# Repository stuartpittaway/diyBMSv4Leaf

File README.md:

# diyBMS v4

Version 4 of the diyBMS for Nissan Leaf Cells

Do it yourself battery management system for Lithium ion battery packs/cells

This circuit revision has been made by George Boudreau - using the original v4 BMS design by Stuart Pittaway.

To contact George, please message on https://community.openenergymonitor.org/

# Videos on how to use and build

https://www.youtube.com/stuartpittaway

# CODE/SOFTWARE

Software and code for the modules and controller can now be found in a seperate repo

https://github.com/stuartpittaway/diyBMSv4Code

# WARNING

This is a DIY product/solution so don’t use this for safety critical systems or in any situation where there could be a risk to life.  

There is no warranty, it may not work as expected or at all.

The use of this project is done so entirely at your own risk.  It may involve electrical voltages which could kill - if in doubt, seek help.

The use of this project may not be compliant with local laws or regulations - if in doubt, seek help.

# License

This work is licensed under a Creative Commons Attribution-NonCommercial-ShareAlike 2.0 UK: England & Wales License.

https://creativecommons.org/licenses/by-nc-sa/2.0/uk/

You are free to:
* Share — copy and redistribute the material in any medium or format
* Adapt — remix, transform, and build upon the material
The licensor cannot revoke these freedoms as long as you follow the license terms.

Under the following terms:
* Attribution — You must give appropriate credit, provide a link to the license, and indicate if changes were made. You may do so in any reasonable manner, but not in any way that suggests the licensor endorses you or your use.
* Non-Commercial — You may not use the material for commercial purposes.
* ShareAlike — If you remix, transform, or build upon the material, you must distribute your contributions under the same license as the original.
* No additional restrictions — You may not apply legal terms or technological measures that legally restrict others from doing anything the license permits.

Notices:
You do not have to comply with the license for elements of the material in the public domain or where your use is permitted by an applicable exception or limitation.

No warranties are given. The license may not give you all of the permissions necessary for your intended use. For example, other rights such as publicity, privacy, or moral rights may limit how you use the material.

# Problem

A DIY Powerwall is the DIY construction of a pack of battery cells to create an energy store which can be used via inverters to power electrical items in the home. Generally cells are salvaged/second hand, and typically use Lithium 18650 cells.

Lithium batteries need to be kept at the same voltage level across a parallel pack. This is done by balancing each cell in the pack to raise or lower its voltage to match the others.

Existing balancing solutions are available in the market place, but at a relatively high cost compared to the cost of the battery bank, so this project is to design a low-cost, simple featured BMS/balancer.

# BMS Design

Design Goals: 
* Build upon my existing skill set and knowledge. 
* Building something that others can contribute to using regular standard libraries and off the shelf components.
* Build something that is inheriently safe
* Use platform.io to manage code and libraries
* Use Arduino based libraries and tools 
* Put everything on GITHUB
* Document it (always gets left to the end!)

# How it works

Controller provides human interface over Wifi/Web and also integrates with other systems like MQTT, emonCMS and Grafana.

Controller is esp8266-12e (NodeMCU v1) - although could be upgraded to ESP32 if really needed.

Controller should be able to take action on alerts/events to shut down inverters/chargers/fuses.

Each cell in a battery pack has a monitoring module.  This uses AVR ATTINY841 linked together by optoisolated serial ports for communication.

ATTINY841 provides:
* internal temperature monitoring
* external temperature monitoring
* Spare input/output for 3rd party use
* autonomous cell voltage balancing - it should still work even if controller is down

# How as v4 improved over v3?

* Code is better!
* Web interface no longer requires access to internet to download javascript libraries
* Controller provides outputs for integration with relay boards and switch gear
* Rules to control relay outputs
* Cell modules use ATTINY841 chip which provides more pins and lower power usage
* Removal of 3.3v regulator and ADUM chips lowers current usage significantly
* v3 module uses 10-12mA current constantly and v4 uses <1mA
* Dual temperature monitoring board + cells

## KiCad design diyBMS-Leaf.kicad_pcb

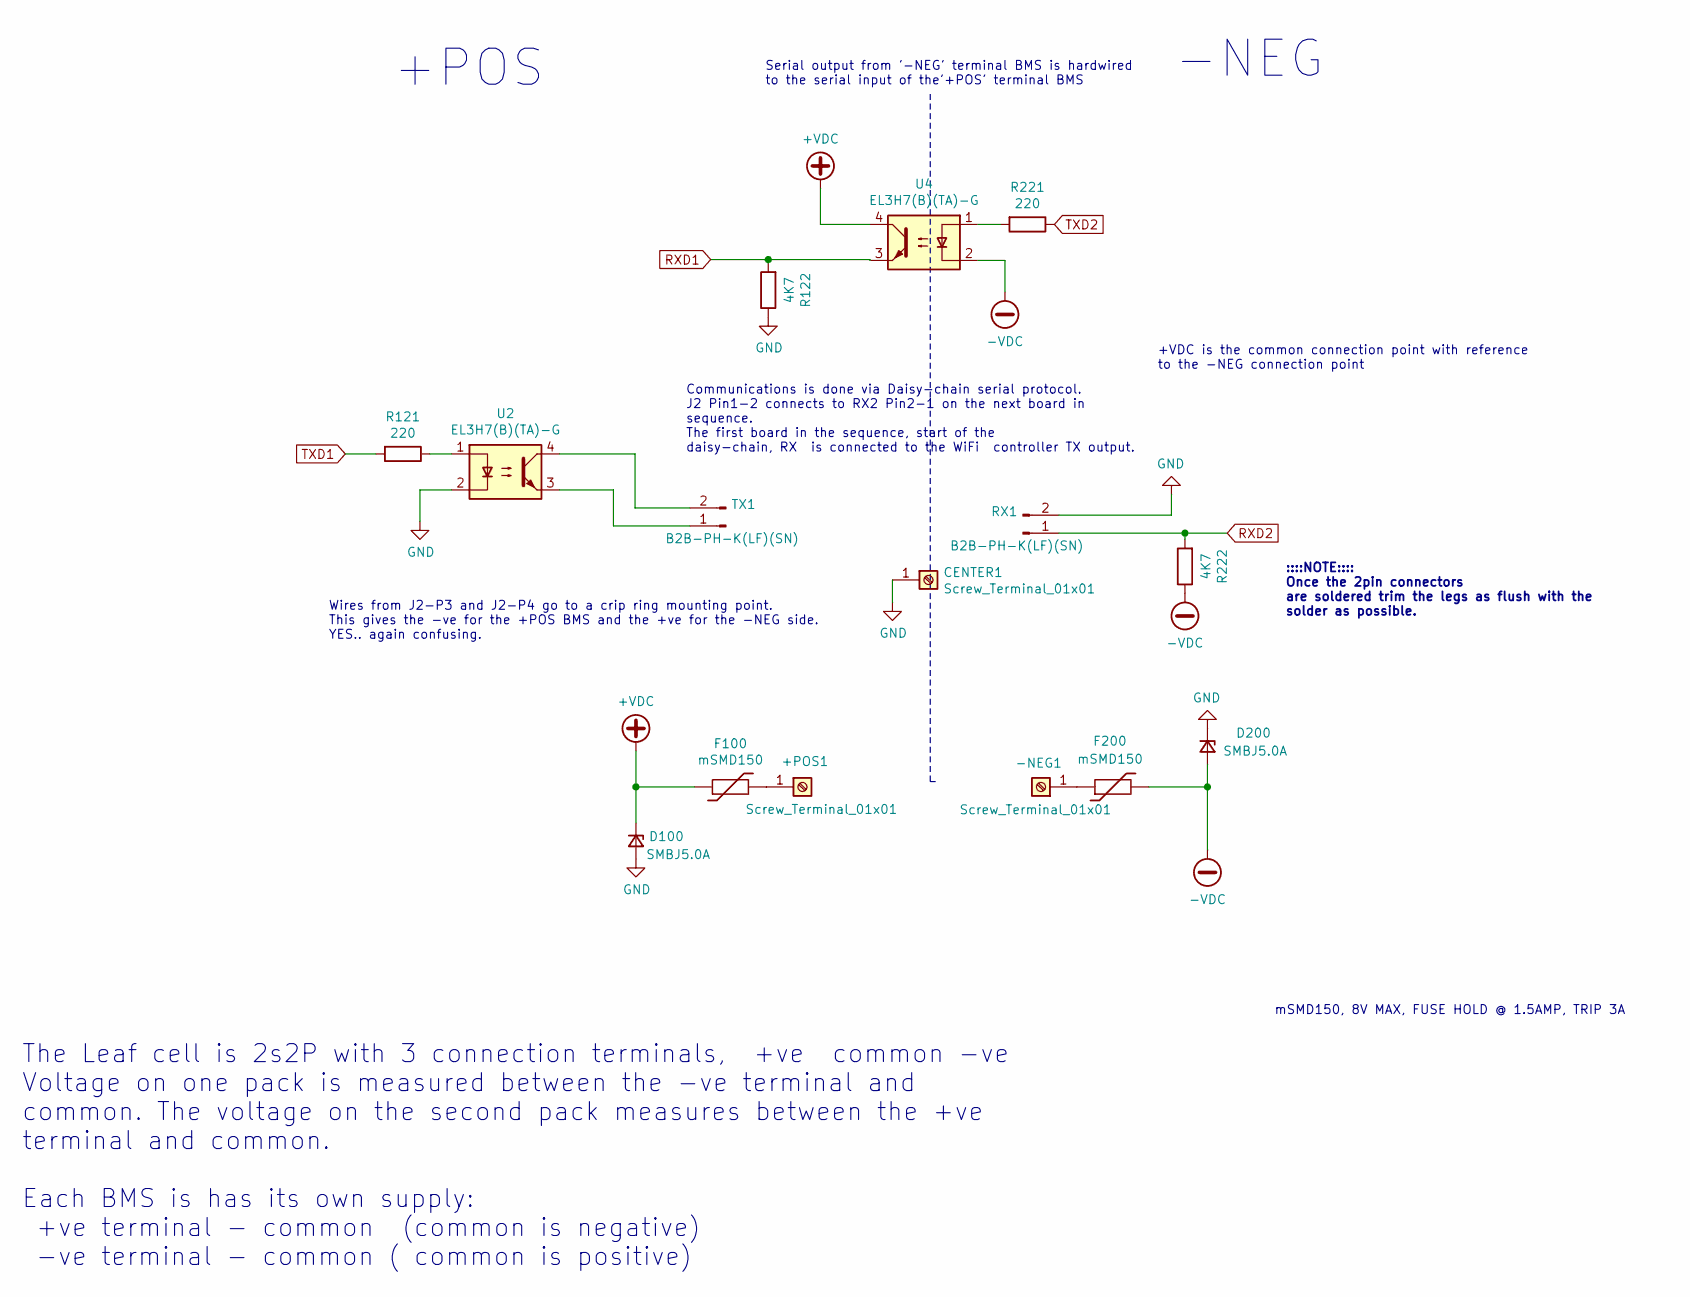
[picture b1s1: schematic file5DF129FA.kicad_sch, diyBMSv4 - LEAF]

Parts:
+POS1: Screw_Terminal_01x01; MountingHole_6.5mm_Pad_Via
-NEG1: Screw_Terminal_01x01; MountingHole_6.5mm_Pad_Via
CENTER1: Screw_Terminal_01x01; MountingHole_6.5mm_Pad_Via
D100, D200: SMBJ5.0A; D_SMB; LCSCStockCode C440263
F100, F200: mSMD150; Fuse_1812_4532Metric; PartNumber mSMD150; LCSCStockCode C70121
R121, R221: 220; R_0805_2012Metric; LCSCStockCode 0805W8F2200T5E
R122, R222: 4K7; R_0805_2012Metric; PartNumber ERJP06F4701V; LCSCStockCode C441984
RX1: B2B-PH-K(LF)(SN); JST_PH_B2B-PH-K_1x02_P2.00mm_Vertical; LCSCStockCode C2683610
TX1: B2B-PH-K(LF)(SN); JST_PH_B2B-PH-K_1x02_P2.00mm_Vertical; LCSCStockCode C2683610
U2, U4: EL3H7(B)(TA)-G; SOP-4_4.4x2.6mm_P1.27mm; LCSCStockCode C32565

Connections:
+VDC: D100.1 (K), F100.1, U4.4; also elsewhere on the board
-VDC: D200.2 (A), F200.2, R222.1, U4.2; also elsewhere on the board
GND: CENTER1.1, D100.2 (A), D200.1 (K), R122.1, RX1.2, U2.2; also elsewhere on the board
unnamed: +POS1.1, F100.2
unnamed: -NEG1.1, F200.1
unnamed: R121.1, U2.1
unnamed: R221.2, U4.1
unnamed: TX1.1, U2.3
unnamed: TX1.2, U2.4
RXD1: R122.2, U4.3; also elsewhere on the board
RXD2: R222.2, RX1.1; also elsewhere on the board
TXD1: R121.2; also elsewhere on the board
TXD2: R221.1; also elsewhere on the board

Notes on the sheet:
The Leaf cell is 2s2P with 3 connection terminals, +ve common -ve Voltage on one pack is measured between the -ve terminal and common. The voltage on the second pack measures between the +ve terminal and common. Each BMS is has its own supply: +ve terminal - common (common is negative) -ve terminal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
Wires from J2-P3 and J2-P4 go to a crip ring mounting point. This gives the -ve for the +POS BMS and the +ve for the -NEG side. YES.. again confusing.
+POS
Communications is done via Daisy-chain serial protocol. J2 Pin1-2 connects to RX2 Pin2-1 on the next board in sequence. The first board in the sequence, start of the daisy-chain, RX is connected to the WiFi controller TX output.
Serial output from '-NEG' terminal BMS is hardwired to the serial input of the'+POS' terminal BMS
+VDC is the common connection point with reference to the -NEG connection point
-NEG
::::NOTE:::: Once the 2pin connectors are soldered trim the legs as flush with the solder as possible.
mSMD150, 8V MAX, FUSE HOLD @ 1.5AMP, TRIP 3A

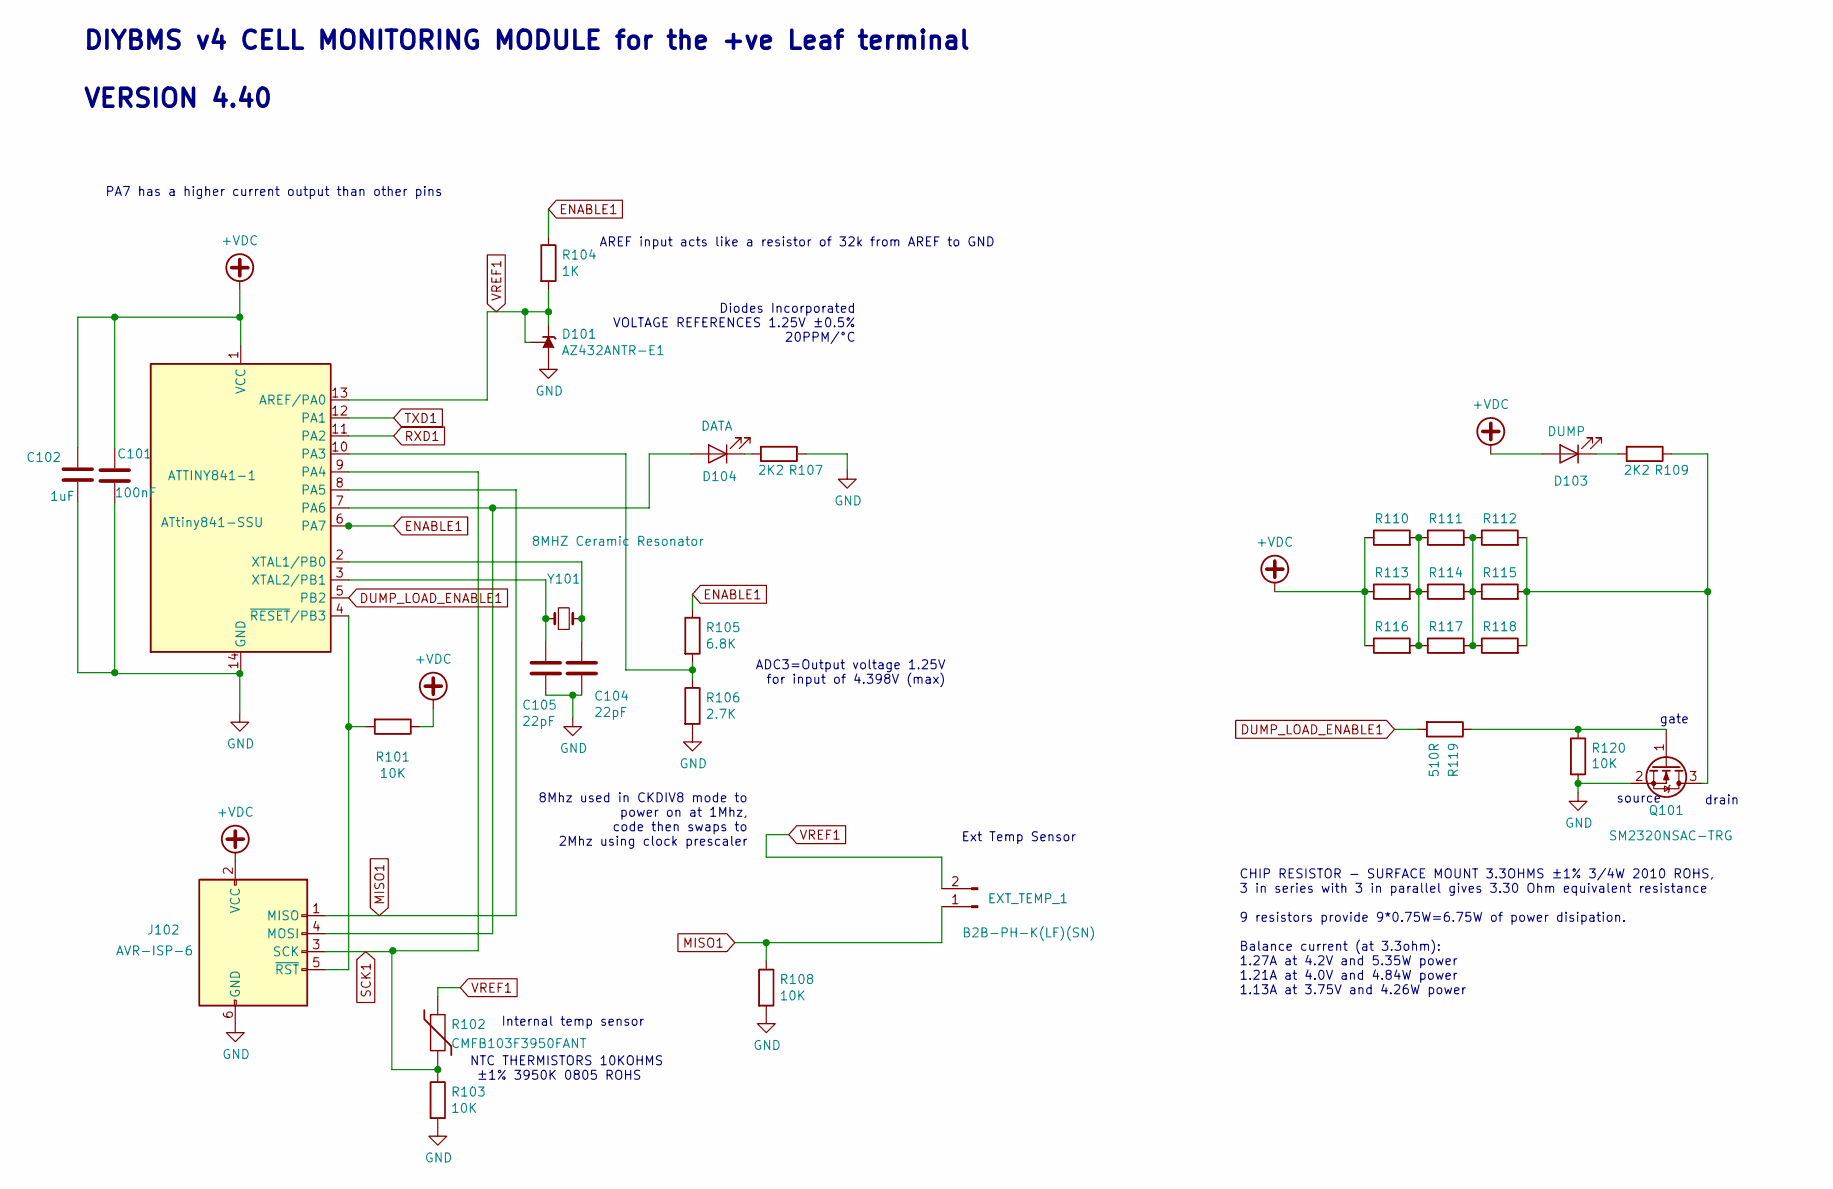
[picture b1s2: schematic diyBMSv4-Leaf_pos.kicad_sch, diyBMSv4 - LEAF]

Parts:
ATTINY841-1: ATtiny841-SSU; SOIC-14_3.9x8.7mm_P1.27mm; LCSCStockCode C219103
C101: 100nF; C_0805_2012Metric; PartNumber CC0805KRX7R9BB104; LCSCStockCode C49678
C102: 1uF; C_0805_2012Metric; PartNumber CL21B105KBFNNNE; LCSCStockCode C28323
C104, C105: 22pF; C_0805_2012Metric; PartNumber CL21C220JBANNNC; LCSCStockCode C1804
D101: AZ432ANTR-E1; SOT-23; PartNumber AZ432ANTR-E1; LCSCStockCode C84139
D103: DUMP; LED_0805_2012Metric; PartNumber NCD0805R1; LCSCStockCode C84256
D104: DATA; LED_0805_2012Metric; PartNumber NCD0805B2; LCSCStockCode C84259
EXT_TEMP_1: B2B-PH-K(LF)(SN); JST_PH_B2B-PH-K_1x02_P2.00mm_Vertical; LCSCStockCode C2683610
J102: AVR-ISP-6; PinHeader_2x03_P2.54mm_Vertical; LCSCStockCode C65114
Q101: SM2320NSAC-TRG; SOT-23; PartNumber SM2320NSAC-TRG; LCSCStockCode C368560
R101, R103, R108, R120: 10K; R_0805_2012Metric; PartNumber 0805W8F1002T5E; LCSCStockCode C17414
R102: CMFB103F3950FANT; R_0805_2012Metric; PartNumber CMFB103F3950FANT; LCSCStockCode C51597
R104: 1K; R_0805_2012Metric; PartNumber 0805W8F1001T5E; LCSCStockCode C17513
R105: 6.8K; R_0805_2012Metric; PartNumber 0805W8F6801T5E; LCSCStockCode C17772
R106: 2.7K; R_0805_2012Metric; PartNumber 0805W8F2701T5E; LCSCStockCode C17530
R107, R109: 2K2; R_0805_2012Metric; PartNumber 0805W8F2201T5E; LCSCStockCode C17520
R110, R111, R112, R113, R114, R115, R116, R117, R118: 3.3OHM 3/4W; R_2010_5025Metric; PartNumber 201007F330KT4E; LCSCStockCode C270971
R119: 510R; R_0805_2012Metric; PartNumber 0805W8F5100T5E; LCSCStockCode C17734
Y101: 8MHZ Ceramic Resonator; Crystal_SMD_5032-2Pin_5.0x3.2mm; PartNumber X50328MSB2GI; LCSCStockCode C115962

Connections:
+VDC: ATTINY841-1.1 (VCC), C101.1, C102.1, D103.2 (A), J102.2 (VCC), R101.1, R110.1, R113.1, R116.1; also elsewhere on the board
DUMP_LOAD_ENABLE1: ATTINY841-1.5 (PB2), R119.2
ENABLE1: ATTINY841-1.6 (PA7), R104.1, R105.1
GND: ATTINY841-1.14 (GND), C101.2, C102.2, C104.2, C105.2, D101.3 (A), J102.6 (GND), Q101.2 (S), R103.2, R106.2, R107.1, R108.2, R120.2; also elsewhere on the board
MISO1: ATTINY841-1.8 (PA5), EXT_TEMP_1.1, J102.1 (MISO), R108.1
unnamed: ATTINY841-1.2 (XTAL1/PB0), C104.1, Y101.2
unnamed: ATTINY841-1.3 (XTAL2/PB1), C105.1, Y101.1
unnamed: ATTINY841-1.4 (~RESET~/PB3), J102.5 (~RST), R101.2
unnamed: ATTINY841-1.7 (PA6), D104.2 (A), J102.4 (MOSI)
unnamed: ATTINY841-1.10 (PA3), R105.2, R106.1
unnamed: D103.1 (K), R109.2
unnamed: D104.1 (K), R107.2
unnamed: Q101.1 (G), R119.1, R120.1
unnamed: Q101.3 (D), R109.1, R112.2, R115.2, R118.2
unnamed: R110.2, R111.1, R113.2, R114.1, R116.2, R117.1
unnamed: R111.2, R112.1, R114.2, R115.1, R117.2, R118.1
RXD1: ATTINY841-1.11 (PA2); also elsewhere on the board
SCK1: ATTINY841-1.9 (PA4), J102.3 (SCK), R102.2, R103.1
TXD1: ATTINY841-1.12 (PA1); also elsewhere on the board
VREF1: ATTINY841-1.13 (AREF/PA0), D101.1 (REF), D101.2 (K), EXT_TEMP_1.2, R102.1, R104.2

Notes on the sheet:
DIYBMS v4 CELL MONITORING MODULE for the +ve Leaf terminal VERSION 4.40
PA7 has a higher current output than other pins
NTC THERMISTORS 10KOHMS ±1% 3950K 0805 ROHS
Internal temp sensor
AREF input acts like a resistor of 32k from AREF to GND
8Mhz used in CKDIV8 mode to power on at 1Mhz, code then swaps to 2Mhz using clock prescaler
Diodes Incorporated VOLTAGE REFERENCES 1.25V ±0.5% 20PPM/°C
ADC3=Output voltage 1.25V for input of 4.398V (max)
Ext Temp Sensor
CHIP RESISTOR - SURFACE MOUNT 3.3OHMS ±1% 3/4W 2010 ROHS, 3 in series with 3 in parallel gives 3.30 Ohm equivalent resistance 9 resistors provide 9*0.75W=6.75W of power disipation. Balance current (at 3.3ohm): 1.27A at 4.2V and 5.35W power 1.21A at 4.0V and 4.84W power 1.13A at 3.75V and 4.26W power
source
gate
drain

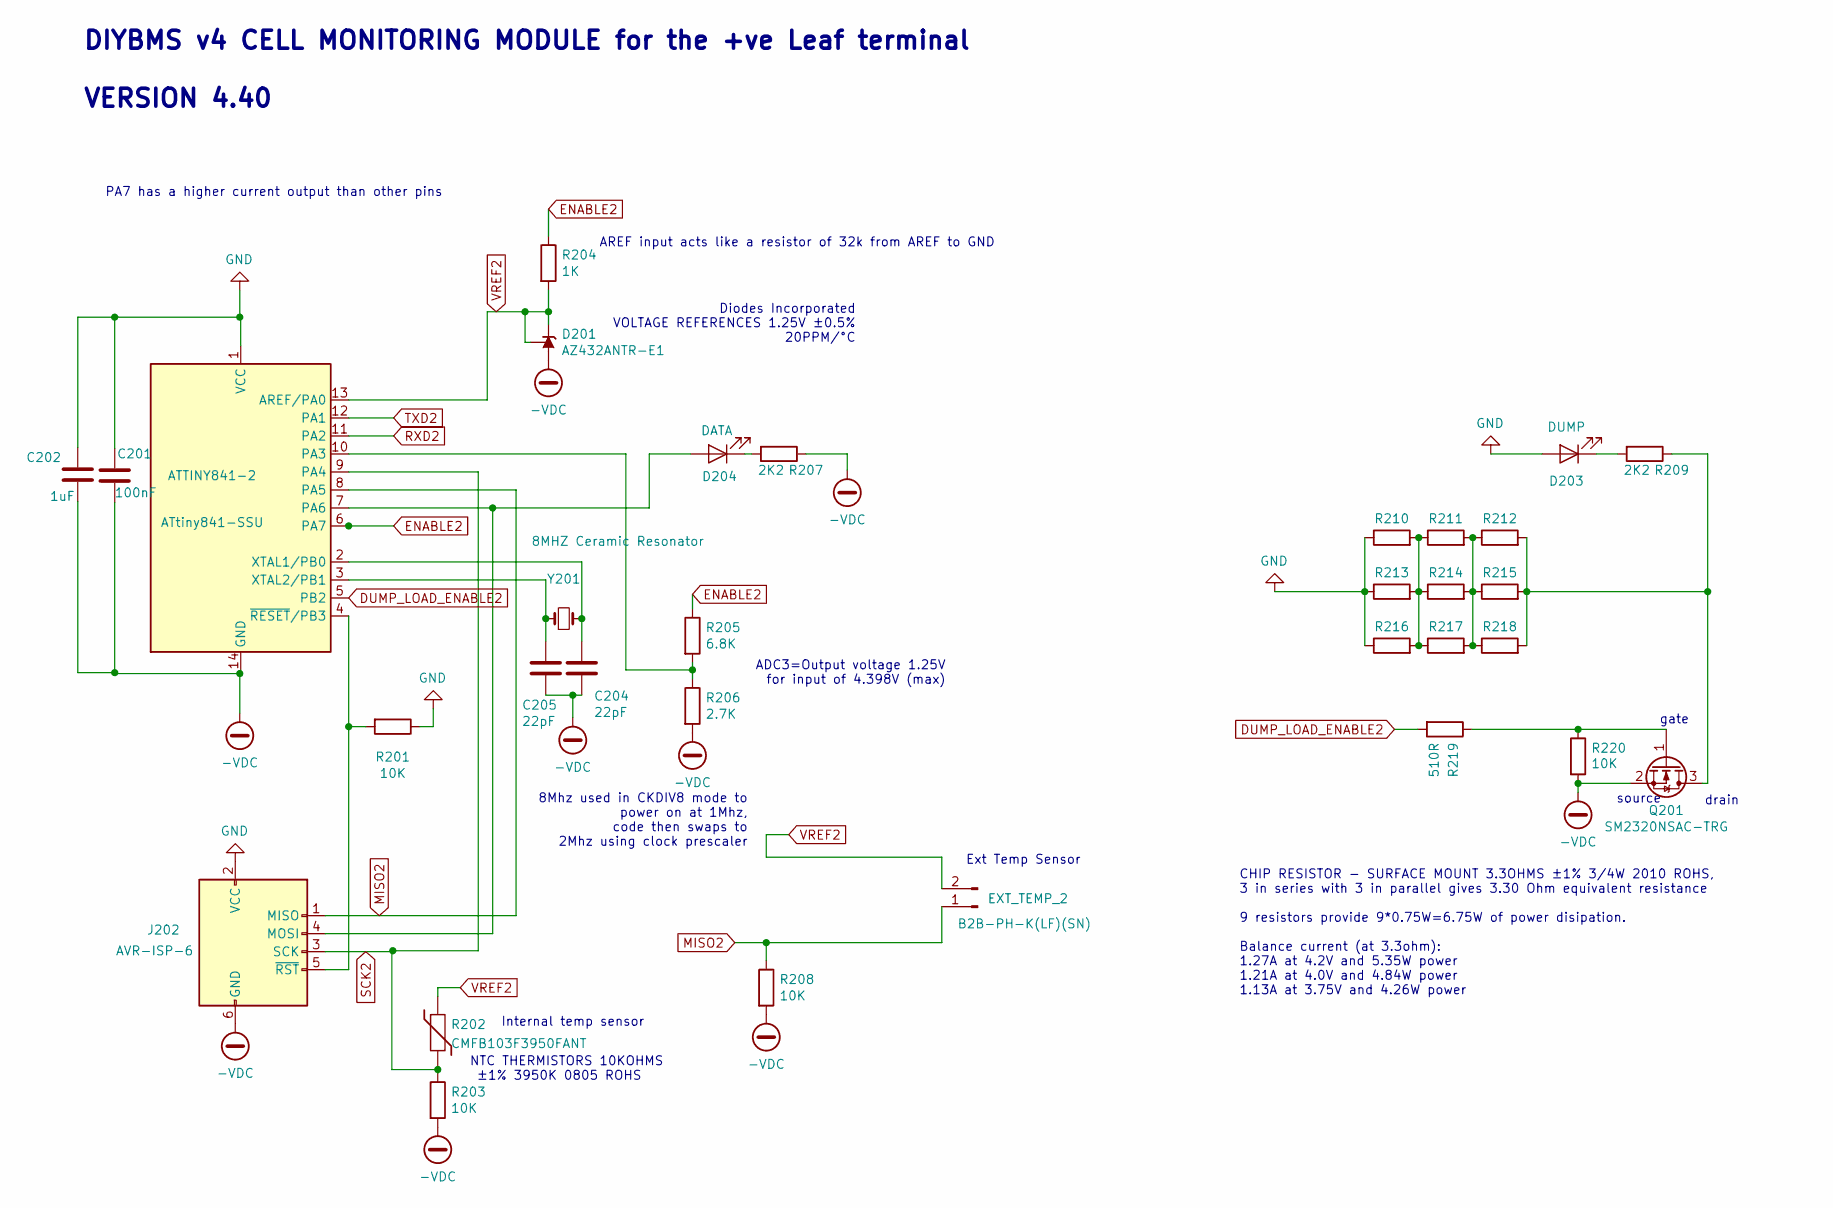
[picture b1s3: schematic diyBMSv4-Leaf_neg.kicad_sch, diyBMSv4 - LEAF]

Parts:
ATTINY841-2: ATtiny841-SSU; SOIC-14_3.9x8.7mm_P1.27mm; LCSCStockCode C219103
C201: 100nF; C_0805_2012Metric; PartNumber CC0805KRX7R9BB104; LCSCStockCode C49678
C202: 1uF; C_0805_2012Metric; PartNumber CL21B105KBFNNNE; LCSCStockCode C28323
C204, C205: 22pF; C_0805_2012Metric; PartNumber CL21C220JBANNNC; LCSCStockCode C1804
D201: AZ432ANTR-E1; SOT-23; PartNumber AZ432ANTR-E1; LCSCStockCode C84139
D203: DUMP; LED_0805_2012Metric; PartNumber NCD0805R1; LCSCStockCode C84256
D204: DATA; LED_0805_2012Metric; PartNumber NCD0805B2; LCSCStockCode C84259
EXT_TEMP_2: B2B-PH-K(LF)(SN); JST_PH_B2B-PH-K_1x02_P2.00mm_Vertical; LCSCStockCode C2683610
J202: AVR-ISP-6; PinHeader_2x03_P2.54mm_Vertical; LCSCStockCode C65114
Q201: SM2320NSAC-TRG; SOT-23; PartNumber SM2320NSAC-TRG; LCSCStockCode C368560
R201, R203, R208, R220: 10K; R_0805_2012Metric; PartNumber 0805W8F1002T5E; LCSCStockCode C17414
R202: CMFB103F3950FANT; R_0805_2012Metric; PartNumber CMFB103F3950FANT; LCSCStockCode C51597
R204: 1K; R_0805_2012Metric; PartNumber 0805W8F1001T5E; LCSCStockCode C17513
R205: 6.8K; R_0805_2012Metric; PartNumber 0805W8F6801T5E; LCSCStockCode C17772
R206: 2.7K; R_0805_2012Metric; PartNumber 0805W8F2701T5E; LCSCStockCode C17530
R207, R209: 2K2; R_0805_2012Metric; PartNumber 0805W8F2201T5E; LCSCStockCode C17520
R210, R211, R212, R213, R214, R215, R216, R217, R218: 3.3OHM 3/4W; R_2010_5025Metric; PartNumber 201007F330KT4E; LCSCStockCode C270971
R219: 510R; R_0805_2012Metric; PartNumber 0805W8F5100T5E; LCSCStockCode C17734
Y201: 8MHZ Ceramic Resonator; Crystal_SMD_5032-2Pin_5.0x3.2mm; PartNumber X50328MSB2GI; LCSCStockCode C115962

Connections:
-VDC: ATTINY841-2.14 (GND), C201.2, C202.2, C204.2, C205.2, D201.3 (A), J202.6 (GND), Q201.2 (S), R203.2, R206.2, R207.1, R208.2, R220.2; also elsewhere on the board
DUMP_LOAD_ENABLE2: ATTINY841-2.5 (PB2), R219.2
ENABLE2: ATTINY841-2.6 (PA7), R204.1, R205.1
GND: ATTINY841-2.1 (VCC), C201.1, C202.1, D203.2 (A), J202.2 (VCC), R201.1, R210.1, R213.1, R216.1; also elsewhere on the board
MISO2: ATTINY841-2.8 (PA5), EXT_TEMP_2.1, J202.1 (MISO), R208.1
unnamed: ATTINY841-2.2 (XTAL1/PB0), C204.1, Y201.2
unnamed: ATTINY841-2.3 (XTAL2/PB1), C205.1, Y201.1
unnamed: ATTINY841-2.4 (~RESET~/PB3), J202.5 (~RST), R201.2
unnamed: ATTINY841-2.7 (PA6), D204.2 (A), J202.4 (MOSI)
unnamed: ATTINY841-2.10 (PA3), R205.2, R206.1
unnamed: D203.1 (K), R209.2
unnamed: D204.1 (K), R207.2
unnamed: Q201.1 (G), R219.1, R220.1
unnamed: Q201.3 (D), R209.1, R212.2, R215.2, R218.2
unnamed: R210.2, R211.1, R213.2, R214.1, R216.2, R217.1
unnamed: R211.2, R212.1, R214.2, R215.1, R217.2, R218.1
RXD2: ATTINY841-2.11 (PA2); also elsewhere on the board
SCK2: ATTINY841-2.9 (PA4), J202.3 (SCK), R202.2, R203.1
TXD2: ATTINY841-2.12 (PA1); also elsewhere on the board
VREF2: ATTINY841-2.13 (AREF/PA0), D201.1 (REF), D201.2 (K), EXT_TEMP_2.2, R202.1, R204.2

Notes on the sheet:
DIYBMS v4 CELL MONITORING MODULE for the +ve Leaf terminal VERSION 4.40
PA7 has a higher current output than other pins
NTC THERMISTORS 10KOHMS ±1% 3950K 0805 ROHS
Internal temp sensor
AREF input acts like a resistor of 32k from AREF to GND
8Mhz used in CKDIV8 mode to power on at 1Mhz, code then swaps to 2Mhz using clock prescaler
Diodes Incorporated VOLTAGE REFERENCES 1.25V ±0.5% 20PPM/°C
ADC3=Output voltage 1.25V for input of 4.398V (max)
Ext Temp Sensor
CHIP RESISTOR - SURFACE MOUNT 3.3OHMS ±1% 3/4W 2010 ROHS, 3 in series with 3 in parallel gives 3.30 Ohm equivalent resistance 9 resistors provide 9*0.75W=6.75W of power disipation. Balance current (at 3.3ohm): 1.27A at 4.2V and 5.35W power 1.21A at 4.0V and 4.84W power 1.13A at 3.75V and 4.26W power
source
gate
drain

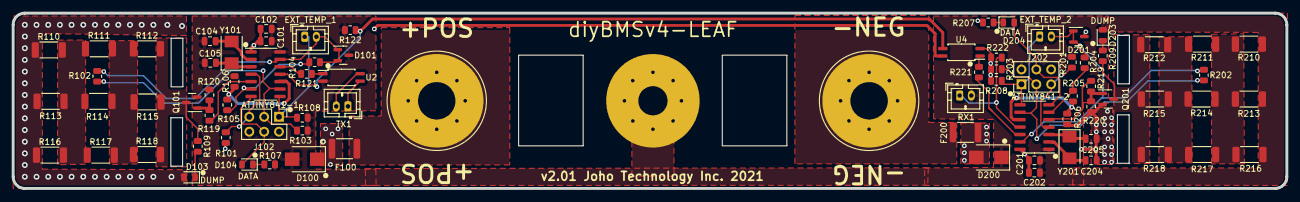
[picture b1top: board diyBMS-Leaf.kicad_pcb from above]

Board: 2 copper layers, 218.0 x 30.0 mm, 79 parts (0 on the bottom side), 45 nets.

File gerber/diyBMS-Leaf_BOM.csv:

Comment,Designator,Footprint,LCSC
"ATtiny841-SSU","ATTINY841-1,ATTINY841-2","Package_SO:SOIC-14_3.9x8.7mm_P1.27mm","C219103"
"100nF","C101,C201","Capacitor_SMD:C_0805_2012Metric","C49678"
"1uF","C102,C202","Capacitor_SMD:C_0805_2012Metric","C28323"
"22pF","C104,C105,C204,C205","Capacitor_SMD:C_0805_2012Metric","C1804"
"SMBJ5.0A","D100,D200","Diode_SMD:D_SMB","C440263"
"AZ432ANTR-E1","D101,D201","Package_TO_SOT_SMD:SOT-23","C84139"
"DUMP","D103,D203","LED_SMD:LED_0805_2012Metric","C84256"
"DATA","D104,D204","LED_SMD:LED_0805_2012Metric","C84259"
"B2B-PH-K(LF)(SN)","EXT_TEMP_1,RX1,TX1,EXT_TEMP_2","Connector_JST:JST_PH_B2B-PH-K_1x02_P2.00mm_Vertical","C2683610"
"mSMD150","F100,F200","Fuse:Fuse_1812_4532Metric","C70121"
"AVR-ISP-6","J102,J202","Connector_PinHeader_2.54mm:PinHeader_2x03_P2.54mm_Vertical","C65114"
"SM2320NSAC-TRG","Q101,Q201","Package_TO_SOT_SMD:SOT-23","C368560"
"10K","R101,R103,R108,R120,R201,R203,R208,R220","Resistor_SMD:R_0805_2012Metric","C17414"
"CMFB103F3950FANT","R102,R202","Resistor_SMD:R_0805_2012Metric","C51597"
"1K","R104,R204","Resistor_SMD:R_0805_2012Metric","C17513"
"6.8K","R105,R205","Resistor_SMD:R_0805_2012Metric","C17772"
"2.7K","R106,R206","Resistor_SMD:R_0805_2012Metric","C17530"
"2K2","R107,R109,R207,R209","Resistor_SMD:R_0805_2012Metric","C17520"
"3.3OHM 3/4W","R110,R111,R112,R113,R114,R115,R116,R117,R118,R210,R211,R212,R213,R214,R215,R216,R217,R218","Resistor_SMD:R_2010_5025Metric","C270971"
"510R","R119,R219","Resistor_SMD:R_0805_2012Metric","C17734"
"220","R121,R221","Resistor_SMD:R_0805_2012Metric","0805W8F2200T5E"
"4K7","R122,R222","Resistor_SMD:R_0805_2012Metric","C441984"
"EL3H7(B)(TA)-G","U2,U4","Package_SO:SOP-4_4.4x2.6mm_P1.27mm","C32565"
"8MHZ Ceramic Resonator","Y101,Y201","Crystal:Crystal_SMD_5032-2Pin_5.0x3.2mm","C115962"

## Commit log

2020-03-15 Initial revision
2021-03-10 Updated with latest
2021-03-11 V2.0.1
2021-03-11 Updated with latest (#3)
    * Updated with latest
    * V2.0.1
